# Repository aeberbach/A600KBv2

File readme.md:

A few years ago I made my first Amiga 1200 mechanical keyboard and soon after people asked me for an A600 keyboard, a kind person loaned me an A600 and I made one.

Here is version 2. At the time of the last keyboard, low-profile keyswitches existed but were hard to find and often could not use MX-stem caps, now it is easier. I'm typing this with a Nuphy Air75 v2 with "Gateron x Nuphy Moss" KS-33 switches and the feel is amazing. There is a lighter variant "Wisteria" and a regular brown tactile option. Blue (clicky) and several variants of linear including red are available too. These switches use a different footprint to standard MX so the PCB had to be redone.

The low profile switches do not come in a 5-pin PCB mount version so a plate is essential. While laser-cut would be amazing I don't have a laser cutter, also that would not be 3-dimensional and would not leave space for the stabilizer wires. To keep it printable on common 3D printers the plate is in two pieces. I have used eSun "milky white" PLA which is opaque and a very good match for an Amiga case. The stabilizers mount to the plates, the holes in the PCB underneath are only for clearance. These plates keep the keyswitches perfectly straight during assembly, improve keyboard stiffness, dampen sound and make for a better appearance.

This keyboard mounts to the case by two 3d printed rails that attach to the top and bottom of the keyboard. They are keyed so as to locate correctly and also to help keep the edges of the plates from lifting. When attaching be careful not to break off the key pieces. Because the plates and rails are printed with PLA the best way to attach is with a small amount of cyanoacrylate glue. If you get too much running into the wrong places your keyboard is toast, so don't use ultra-thin that will wick everywhere and don't use too much! Medium glue will wick enough to secure them.

One thing that hasn't been done is to source a Caps Lock key with a window for the LED. The LED mount is still there and you can put a LED under the switch but I don't know where you can get a windowed keycap for it. The LED section of this keyboard includes a circuit where it will light an alternate LED for power when Caps Lock is active. My keyboard has a green LED for power but that changes to blue when Caps Lock is activated.

If you don't want to use the LED function of this keyboard you can just snip away the top right of the PCB and use the original Amiga 1200 LED PCB. In that case don't bother with LEDs, capacitor, resistors or the inverter chip.

The space bar stabilizer cannot be bought. Instead get a normal 2U stabilizer and remove the wire. Bend a piece of 1mm music wire so that the parallel wires are 133.5mm apart, and trim them to length using the 2U wire as a guide. If you do not get this within about 1/2mm or the parallel wires are not in-plane and actually parallel then your space bar will not work properly!

Requirements:

    one PCB (see the 'fab' folder for gerber files, ready to build)
    78 Gateron KS-33 keyswitches
    2 Gateron 2U plate-mount low-profile stabilizers
    1 more Gateron low-profile stabilizer to disassemble for the space bar
    0805 LEDs: red, green, yellow/orange and blue (or whatever colors you like for the various functions)
    0805 10k resistor (R6) 
    0805 current-limiting resistor for each LED. Choose a value not less than 300 ohms. If your LEDs are too bright you can use higher values. I use 1k ohms, your LEDs may vary.
    0.1uF 0805 decoupling capacitor
    SN74LVC2G04DBVR dual inverter (available Mouser electronics)
    4-pin dupont housing, pins and cable to connect LED section to Amiga
    one FFC connector, 32-way RA 1.25mm pitch. Molex 52044-3245 (available Mouser Electronics)
    one FFC ribbon cable, 30-way. You can trim two circuits from Molex 15168-0400 (available Mouser Electronics) or look on AliExpress.
    Printed plates to house stabilizers and switches on top of PCB (STLs in 3dprint folder)
    Printed mounts to secure the keyboard in your case (STLs in 3dprint folder)
    78 Amiga keycaps: user Steveed on Amibay recently sorted this out with Signature Plastics and I think these are the best available. A1200.net keycaps are for the Mitsumi-style switch and will not fit.

The cost of all this varies with the cost of PCB manufacture, keyswitches and stabilizers and of course the keycaps. As a very rough guide expect to pay no less than about:

    PCB $20
    keyswitches $30
    stabilizers $20
    LEDs and other components $2
    FFC connector and cable $8
    3D printed parts $10

In quantities of one - it gets cheaper when you buy in bulk of course. And assembly will take at least three hours. Obviously this is not cheap and does not even count a quality set of keycaps at around $130. (But if you weren't slightly obsessed you probably wouldn't have an Amiga in 2024.)

The license for this keyboard is non-commercial - no stores may build and sell this project. However if a person has ordered the minimum of 5 PCBs from one of the usual places and wants to offer the extras for sale at near cost, once, that is reasonable.

Thanks to Steveed (Amibay) and to everyone that has supported this project. 

License: CC-BY-NC-SA 4.0

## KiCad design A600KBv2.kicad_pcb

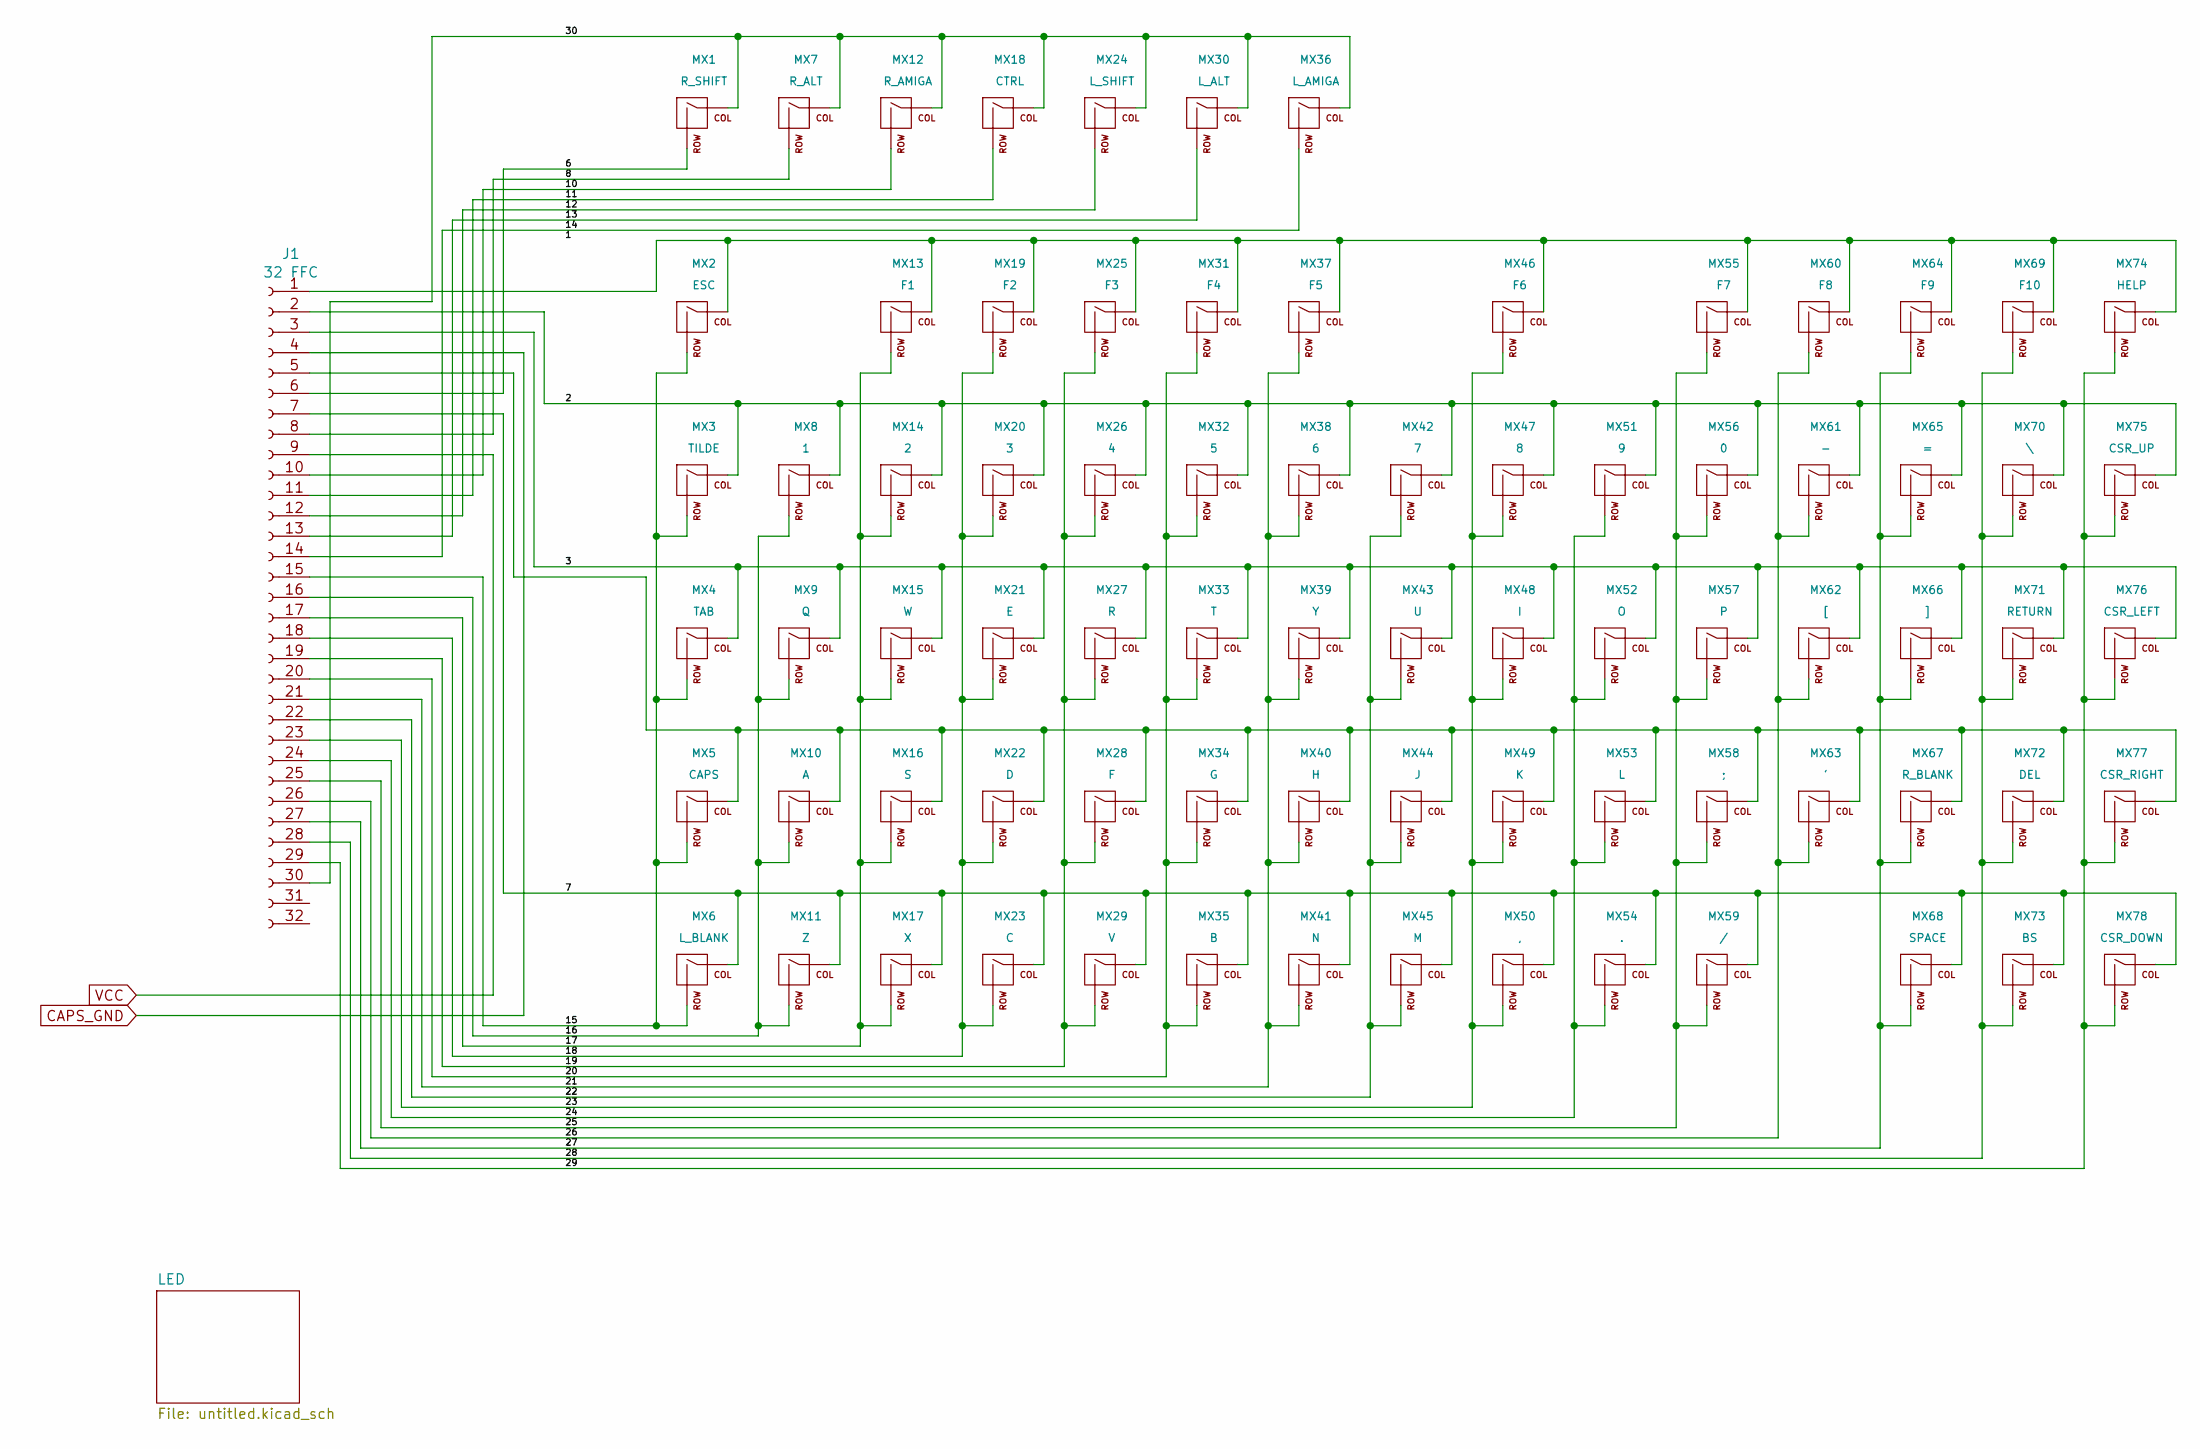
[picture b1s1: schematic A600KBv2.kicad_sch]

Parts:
J1: 32 FFC; FFC-1.25mm-RA-5204403245
MX1: R_SHIFT; Gateron-KS33-Solderable-1.75U
MX2: ESC; Gateron-KS33-Solderable-1.25U
MX3: TILDE; Gateron-KS33-Solderable-1.5U
MX4: TAB; Gateron-KS-33-2U-stabilizer
MX5: CAPS; Gateron-KS33-Solderable-1U
MX6: L_BLANK; Gateron-KS33-Solderable-1U
MX7: R_ALT; Gateron-KS33-Solderable-1U
MX8: 1; Gateron-KS33-Solderable-1U
MX9: Q; Gateron-KS33-Solderable-1U
MX10: A; Gateron-KS33-Solderable-1U
MX11: Z; Gateron-KS33-Solderable-1U
MX12: R_AMIGA; Gateron-KS33-Solderable-1.25U
MX13: F1; Gateron-KS33-Solderable-1.25U
MX14: 2; Gateron-KS33-Solderable-1U
MX15: W; Gateron-KS33-Solderable-1U
MX16: S; Gateron-KS33-Solderable-1U
MX17: X; Gateron-KS33-Solderable-1U
MX18: CTRL; Gateron-KS33-Solderable-1.25U
MX19: F2; Gateron-KS33-Solderable-1.25U
MX20: 3; Gateron-KS33-Solderable-1U
MX21: E; Gateron-KS33-Solderable-1U
MX22: D; Gateron-KS33-Solderable-1U
MX23: C; Gateron-KS33-Solderable-1U
MX24: L_SHIFT; Gateron-KS33-Solderable-1.75U
MX25: F3; Gateron-KS33-Solderable-1.25U
MX26: 4; Gateron-KS33-Solderable-1U
MX27: R; Gateron-KS33-Solderable-1U
MX28: F; Gateron-KS33-Solderable-1U
MX29: V; Gateron-KS33-Solderable-1U
MX30: L_ALT; Gateron-KS33-Solderable-1.25U
MX31: F4; Gateron-KS33-Solderable-1.25U
MX32: 5; Gateron-KS33-Solderable-1U
MX33: T; Gateron-KS33-Solderable-1U
MX34: G; Gateron-KS33-Solderable-1U
MX35: B; Gateron-KS33-Solderable-1U
MX36: L_AMIGA; Gateron-KS33-Solderable-1.25U
MX37: F5; Gateron-KS33-Solderable-1.25U
MX38: 6; Gateron-KS33-Solderable-1U
MX39: Y; Gateron-KS33-Solderable-1U
MX40: H; Gateron-KS33-Solderable-1U
MX41: N; Gateron-KS33-Solderable-1U
MX42: 7; Gateron-KS33-Solderable-1U
MX43: U; Gateron-KS33-Solderable-1U
MX44: J; Gateron-KS33-Solderable-1U
MX45: M; Gateron-KS33-Solderable-1U
MX46: F6; Gateron-KS33-Solderable-1.25U
MX47: 8; Gateron-KS33-Solderable-1U
MX48: I; Gateron-KS33-Solderable-1U
MX49: K; Gateron-KS33-Solderable-1U
MX50: ,; Gateron-KS33-Solderable-1U
MX51: 9; Gateron-KS33-Solderable-1U
MX52: O; Gateron-KS33-Solderable-1U
MX53: L; Gateron-KS33-Solderable-1U
MX54: .; Gateron-KS33-Solderable-1U
MX55: F7; Gateron-KS33-Solderable-1.25U
MX56: 0; Gateron-KS33-Solderable-1U
MX57: P; Gateron-KS33-Solderable-1U
MX58: ;; Gateron-KS33-Solderable-1U
MX59: /; Gateron-KS33-Solderable-1U
MX60: F8; Gateron-KS33-Solderable-1.25U
MX61: -; Gateron-KS33-Solderable-1U
MX62: [; Gateron-KS33-Solderable-1U
MX63: '; Gateron-KS33-Solderable-1U
MX64: F9; Gateron-KS33-Solderable-1.25U
MX65: =; Gateron-KS33-Solderable-1U
MX66: ]; Gateron-KS33-Solderable-1U
MX67: R_BLANK; Gateron-KS33-Solderable-1U
MX68: SPACE; KS-33-8-9U-space
MX69: F10; Gateron-KS33-Solderable-1.25U
MX70: \; Gateron-KS33-Solderable-1U
MX71: RETURN; KS-33-ISO-2U-stabilizer
MX72: DEL; Gateron-KS33-Solderable-1U
MX73: BS; Gateron-KS33-Solderable-1U
MX74: HELP; Gateron-KS33-Solderable-1.25U
MX75: CSR_UP; Gateron-KS33-Solderable-1U
MX76: CSR_LEFT; Gateron-KS33-Solderable-1U
MX77: CSR_RIGHT; Gateron-KS33-Solderable-1U
MX78: CSR_DOWN; Gateron-KS33-Solderable-1U

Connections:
/2: J1.2, MX3.1 (COL), MX8.1 (COL), MX14.1 (COL), MX20.1 (COL), MX26.1 (COL), MX32.1 (COL), MX38.1 (COL), MX42.1 (COL), MX47.1 (COL), MX51.1 (COL), MX56.1 (COL), MX61.1 (COL), MX65.1 (COL), MX70.1 (COL), MX75.1 (COL)
/3: J1.3, MX4.1 (COL), MX9.1 (COL), MX15.1 (COL), MX21.1 (COL), MX27.1 (COL), MX33.1 (COL), MX39.1 (COL), MX43.1 (COL), MX48.1 (COL), MX52.1 (COL), MX57.1 (COL), MX62.1 (COL), MX66.1 (COL), MX71.1 (COL), MX76.1 (COL)
/6: J1.6, MX1.2 (ROW)
/7: J1.7, MX6.1 (COL), MX11.1 (COL), MX17.1 (COL), MX23.1 (COL), MX29.1 (COL), MX35.1 (COL), MX41.1 (COL), MX45.1 (COL), MX50.1 (COL), MX54.1 (COL), MX59.1 (COL), MX68.1 (COL), MX73.1 (COL), MX78.1 (COL); also elsewhere on the board
/8: J1.8, MX7.2 (ROW)
/10: J1.10, MX12.2 (ROW)
/11: J1.11, MX18.2 (ROW)
/12: J1.12, MX24.2 (ROW)
/13: J1.13, MX30.2 (ROW)
/14: J1.14, MX36.2 (ROW)
/15: J1.15, MX2.2 (ROW), MX3.2 (ROW), MX4.2 (ROW), MX5.2 (ROW), MX6.2 (ROW)
/16: J1.16, MX8.2 (ROW), MX9.2 (ROW), MX10.2 (ROW), MX11.2 (ROW)
/17: J1.17, MX13.2 (ROW), MX14.2 (ROW), MX15.2 (ROW), MX16.2 (ROW), MX17.2 (ROW)
/18: J1.18, MX19.2 (ROW), MX20.2 (ROW), MX21.2 (ROW), MX22.2 (ROW), MX23.2 (ROW)
/19: J1.19, MX25.2 (ROW), MX26.2 (ROW), MX27.2 (ROW), MX28.2 (ROW), MX29.2 (ROW)
/20: J1.20, MX31.2 (ROW), MX32.2 (ROW), MX33.2 (ROW), MX34.2 (ROW), MX35.2 (ROW)
/21: J1.21, MX37.2 (ROW), MX38.2 (ROW), MX39.2 (ROW), MX40.2 (ROW), MX41.2 (ROW)
/22: J1.22, MX42.2 (ROW), MX43.2 (ROW), MX44.2 (ROW), MX45.2 (ROW)
/23: J1.23, MX46.2 (ROW), MX47.2 (ROW), MX48.2 (ROW), MX49.2 (ROW), MX50.2 (ROW)
/24: J1.24, MX51.2 (ROW), MX52.2 (ROW), MX53.2 (ROW), MX54.2 (ROW)
/25: J1.25, MX55.2 (ROW), MX56.2 (ROW), MX57.2 (ROW), MX58.2 (ROW), MX59.2 (ROW)
/26: J1.26, MX60.2 (ROW), MX61.2 (ROW), MX62.2 (ROW), MX63.2 (ROW)
/27: J1.27, MX64.2 (ROW), MX65.2 (ROW), MX66.2 (ROW), MX67.2 (ROW), MX68.2 (ROW); also elsewhere on the board
/28: J1.28, MX69.2 (ROW), MX70.2 (ROW), MX71.2 (ROW), MX72.2 (ROW), MX73.2 (ROW)
/29: J1.29, MX74.2 (ROW), MX75.2 (ROW), MX76.2 (ROW), MX77.2 (ROW), MX78.2 (ROW)
/30: J1.30, MX1.1 (COL), MX7.1 (COL), MX12.1 (COL), MX18.1 (COL), MX24.1 (COL), MX30.1 (COL), MX36.1 (COL)
CAPS_GND: J1.4; also elsewhere on the board
unnamed: J1.1, MX2.1 (COL), MX13.1 (COL), MX19.1 (COL), MX25.1 (COL), MX31.1 (COL), MX37.1 (COL), MX46.1 (COL), MX55.1 (COL), MX60.1 (COL), MX64.1 (COL), MX69.1 (COL), MX74.1 (COL)
unnamed: J1.5, MX5.1 (COL), MX10.1 (COL), MX16.1 (COL), MX22.1 (COL), MX28.1 (COL), MX34.1 (COL), MX40.1 (COL), MX44.1 (COL), MX49.1 (COL), MX53.1 (COL), MX58.1 (COL), MX63.1 (COL), MX67.1 (COL), MX72.1 (COL), MX77.1 (COL)
VCC: J1.9; also elsewhere on the board

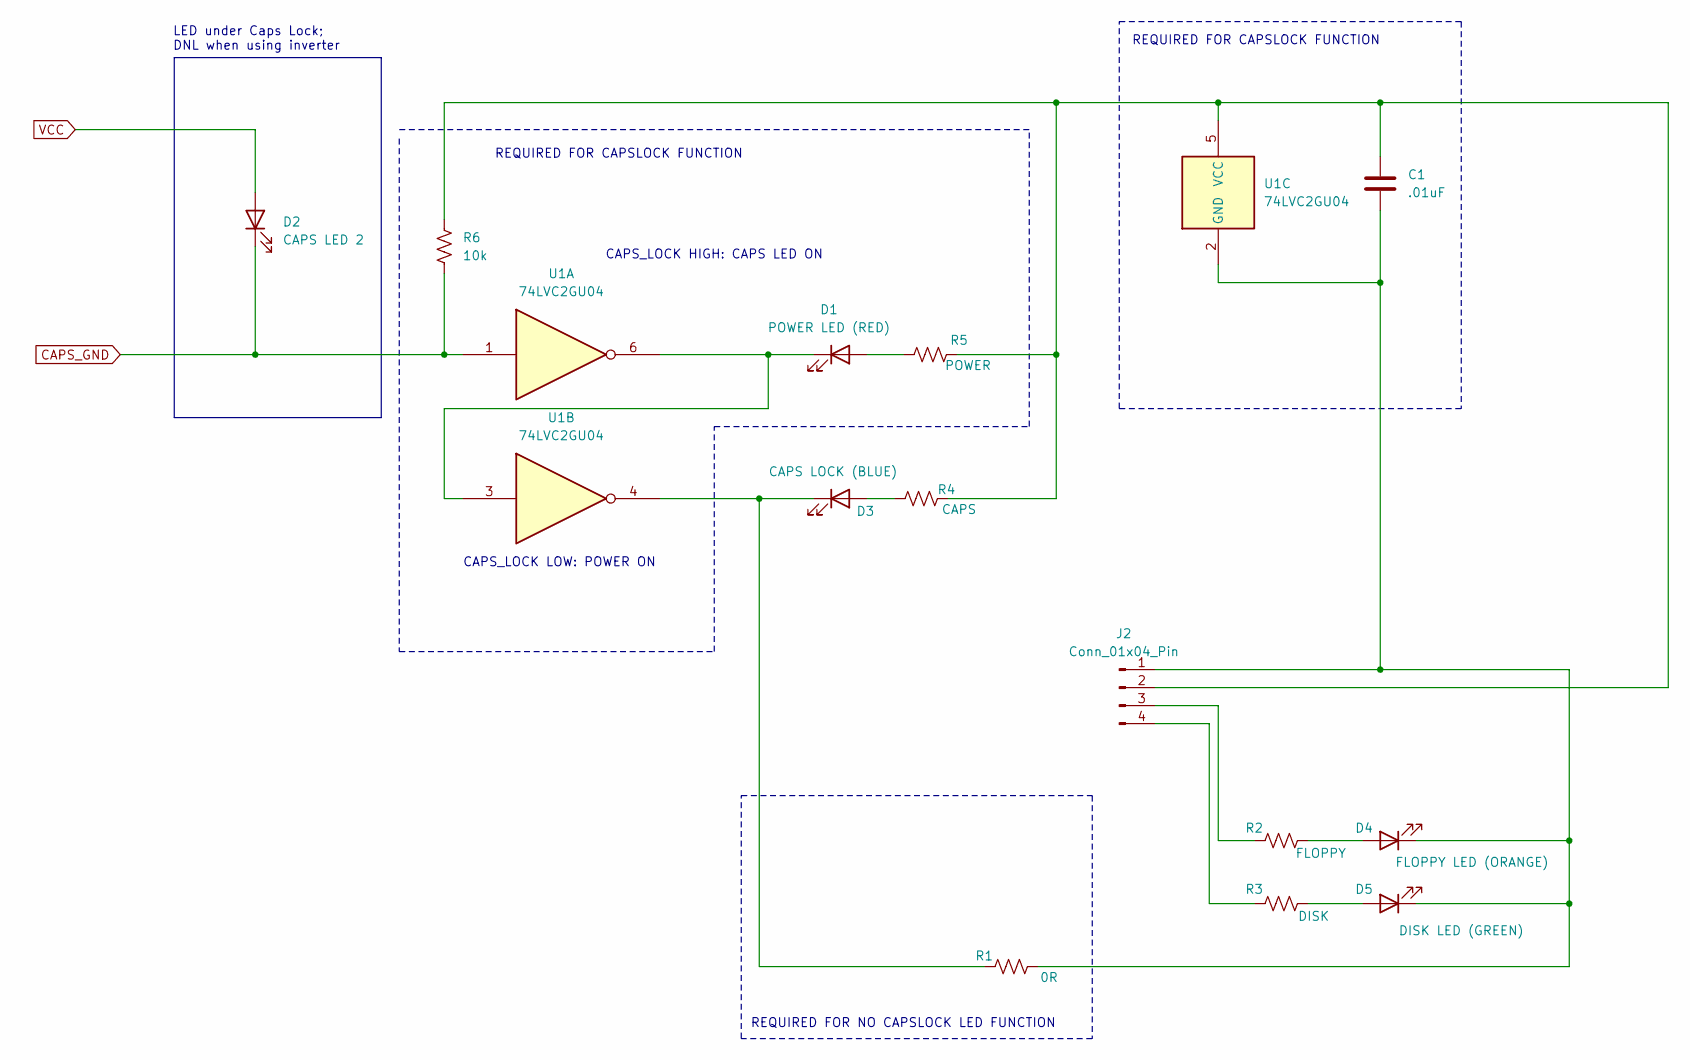
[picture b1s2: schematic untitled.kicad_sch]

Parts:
C1: .01uF; C_0805_2012Metric_Pad1.18x1.45mm_HandSolder
D1: POWER LED (RED); LED_0805_2012Metric
D2: CAPS LED 2; LED_0805_2012Metric
D3: CAPS LOCK (BLUE); LED_0805_2012Metric
D4: FLOPPY LED (ORANGE); LED_0805_2012Metric
D5: DISK LED (GREEN); LED_0805_2012Metric
J2: Conn_01x04_Pin; PinHeader_1x04_P2.54mm_Vertical
R1: 0R; R_0805_2012Metric_Pad1.20x1.40mm_HandSolder
R2: FLOPPY; R_0805_2012Metric_Pad1.20x1.40mm_HandSolder
R3: DISK; R_0805_2012Metric_Pad1.20x1.40mm_HandSolder
R4: CAPS; R_0805_2012Metric_Pad1.20x1.40mm_HandSolder
R5: POWER; R_0805_2012Metric_Pad1.20x1.40mm_HandSolder
R6: 10k; R_0805_2012Metric_Pad1.20x1.40mm_HandSolder
U1: 74LVC2GU04; SOT-23-6

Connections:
CAPS_GND: D2.1 (K), R6.2, U1.1; also elsewhere on the board
unnamed: D1.2 (A), R5.1
unnamed: D1.1 (K), U1.3, U1.6
unnamed: D3.2 (A), R4.1
unnamed: D3.1 (K), R1.1, U1.4
unnamed: D4.2 (A), R2.2
unnamed: C1.2, D4.1 (K), D5.1 (K), J2.1, R1.2, U1.2 (GND)
unnamed: D5.2 (A), R3.2
unnamed: C1.1, J2.2, R4.2, R5.2, R6.1, U1.5 (VCC)
unnamed: J2.3, R2.1
unnamed: J2.4, R3.1
VCC: D2.2 (A); also elsewhere on the board

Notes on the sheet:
REQUIRED FOR CAPSLOCK FUNCTION
LED under Caps Lock; DNL when using inverter
REQUIRED FOR NO CAPSLOCK LED FUNCTION
CAPS_LOCK HIGH: CAPS LED ON
CAPS_LOCK LOW: POWER ON

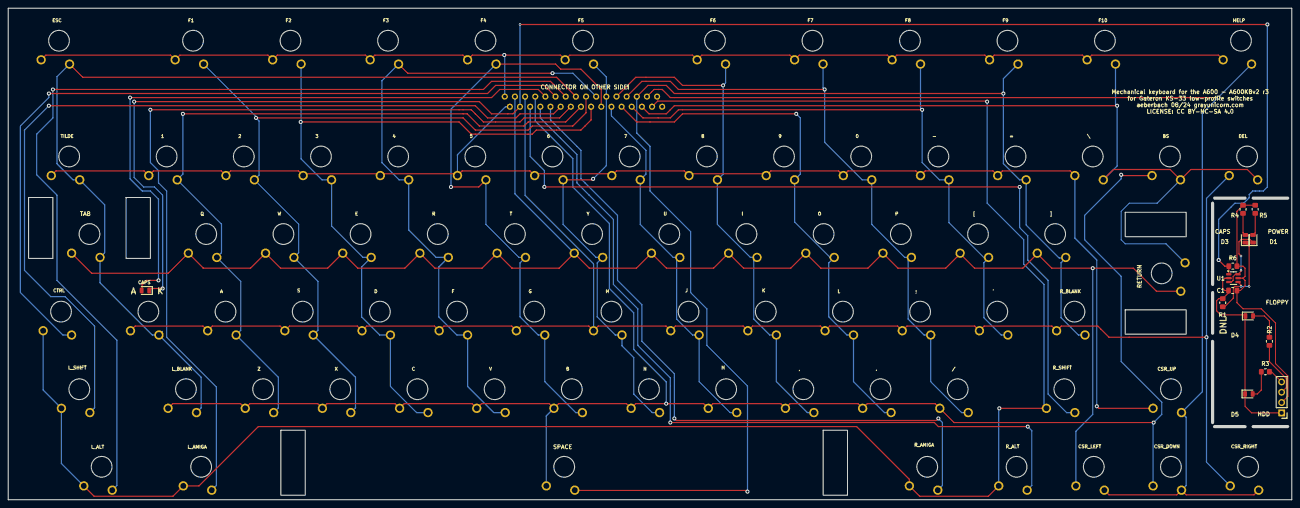
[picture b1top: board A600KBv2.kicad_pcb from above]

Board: 2 copper layers, 315.2 x 120.2 mm, 93 parts (1 on the bottom side), 40 nets.

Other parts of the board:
SPACE: SPACE; KS-33-8-9U-space

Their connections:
/7: SPACE.1 (COL); also elsewhere on the board
/27: SPACE.2 (ROW); also elsewhere on the board

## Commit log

2024-06-26 KiCAD gitignore
2024-06-30 Done and ready to use
    Still needs a better mounting solution. For now glue strips of material to raise PCB.
2024-07-04 r2
    smaller cutouts for stabilizers in PCB
    removed unused mounting holes
    board shorter by 2mm top/bottom to mount rails
    add 0R option to use capslock under keycap only
    silkscreen labels for switches
2024-07-08 fab 9/7/24 KS-33 revised caps LED
2024-08-01 All working with pullups and alt hdd led. New left plate.
2024-08-06 .25 offset stabs, interlocking case rails
2024-08-07 Update plates
2024-08-07 Fix up with pullup resistor for r3
2024-08-07 readme
2024-08-07 remove junk files
2024-08-15 v3 III
2024-10-15 Consistent STL naming, readme update
2024-11-03 sort 3D print files
2025-01-12 final edit
2025-01-12 add license file
